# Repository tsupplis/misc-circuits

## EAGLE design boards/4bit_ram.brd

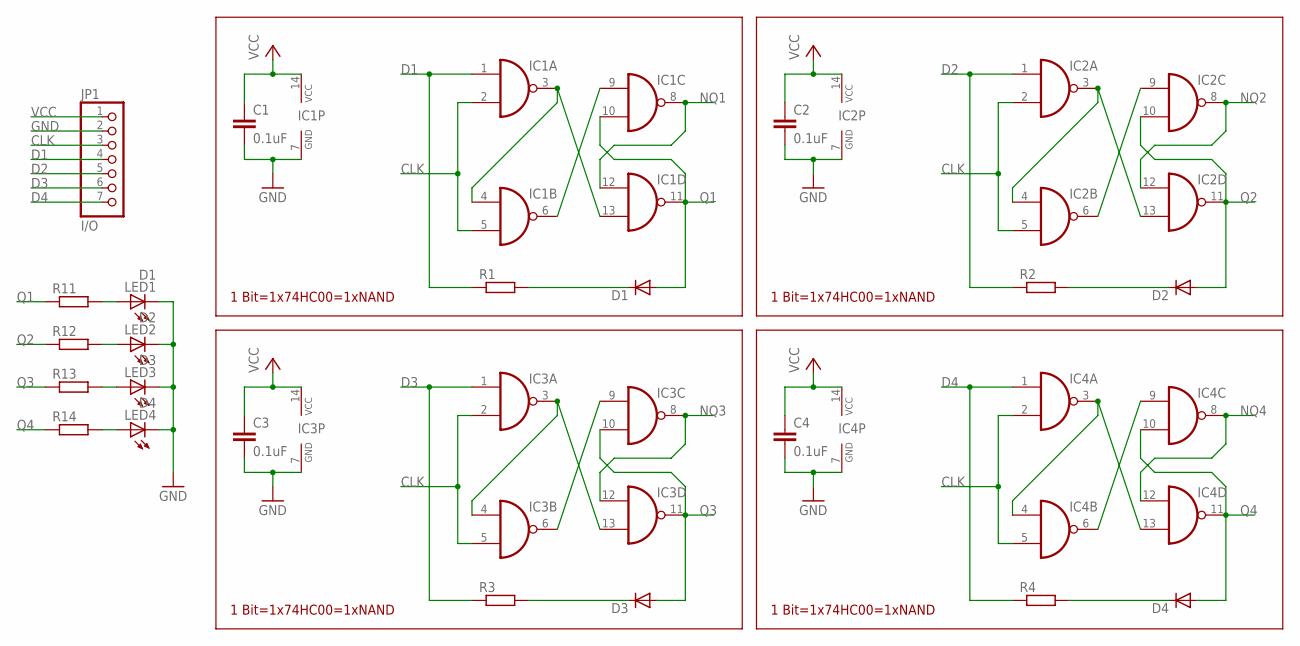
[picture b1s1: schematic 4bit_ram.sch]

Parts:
C1, C2, C3, C4: 0.1uF; C025-025X050
D1, D2, D3, D4: 1N4148DO35-7; DO35-7
IC1, IC2, IC3, IC4: 74HC00N; DIL14
JP1: I/O; 1X07
LED1: D1; LED3MM
LED2: D2; LED3MM
LED3: D3; LED3MM
LED4: D4; LED3MM
R1, R2, R3, R4: 10K; 0204/7
R11, R12, R13, R14: 470; 0204/7

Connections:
CLK: IC1.2 (I1), IC1.5 (I1), IC2.2 (I1), IC2.5 (I1), IC3.2 (I1), IC3.5 (I1), IC4.2 (I1), IC4.5 (I1), JP1.3
D1: IC1.1 (I0), JP1.4, R1.1
D2: IC2.1 (I0), JP1.5, R2.1
D3: IC3.1 (I0), JP1.6, R3.1
D4: IC4.1 (I0), JP1.7, R4.1
GND: C1.2, C2.2, C3.2, C4.2, IC1.7 (GND), IC2.7 (GND), IC3.7 (GND), IC4.7 (GND), JP1.2, LED1.K (C), LED2.K (C), LED3.K (C), LED4.K (C)
unnamed: D1.C, R1.2
unnamed: IC3.6 (O), IC3.9 (I0)
unnamed: IC1.3 (O), IC1.4 (I0), IC1.13 (I1)
unnamed: IC1.6 (O), IC1.9 (I0)
unnamed: IC2.3 (O), IC2.4 (I0), IC2.13 (I1)
unnamed: D2.C, R2.2
unnamed: IC2.6 (O), IC2.9 (I0)
unnamed: IC4.6 (O), IC4.9 (I0)
unnamed: LED1.A, R11.2
unnamed: IC3.3 (O), IC3.4 (I0), IC3.13 (I1)
unnamed: D3.C, R3.2
unnamed: IC4.3 (O), IC4.4 (I0), IC4.13 (I1)
unnamed: D4.C, R4.2
unnamed: LED2.A, R12.2
unnamed: LED3.A, R13.2
unnamed: LED4.A, R14.2
NQ1: IC1.8 (O), IC1.12 (I0)
NQ2: IC2.8 (O), IC2.12 (I0)
NQ3: IC3.8 (O), IC3.12 (I0)
NQ4: IC4.8 (O), IC4.12 (I0)
Q1: D1.A, IC1.10 (I1), IC1.11 (O), R11.1
Q2: D2.A, IC2.10 (I1), IC2.11 (O), R12.1
Q3: D3.A, IC3.10 (I1), IC3.11 (O), R13.1
Q4: D4.A, IC4.10 (I1), IC4.11 (O), R14.1
VCC: C1.1, C2.1, C3.1, C4.1, IC1.14 (VCC), IC2.14 (VCC), IC3.14 (VCC), IC4.14 (VCC), JP1.1

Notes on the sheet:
1 Bit=1x74HC00=1xNAND

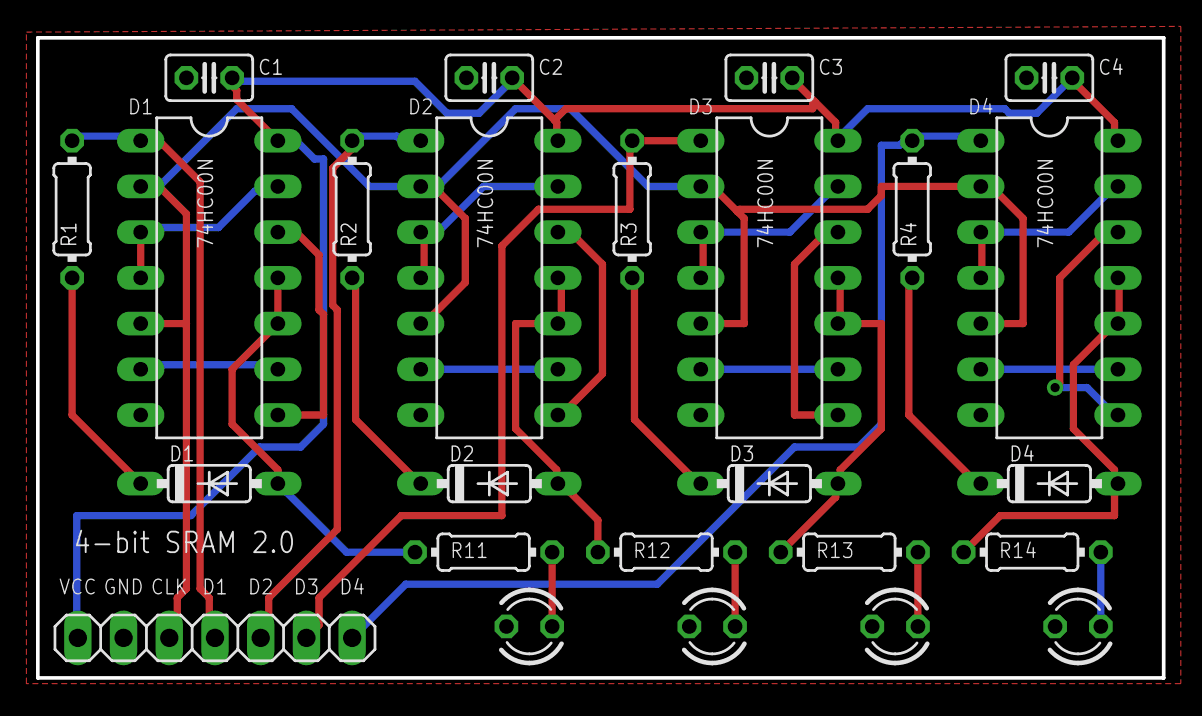
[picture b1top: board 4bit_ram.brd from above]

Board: 2 copper layers, 62.5 x 35.6 mm, 25 parts (0 on the bottom side), 31 nets.

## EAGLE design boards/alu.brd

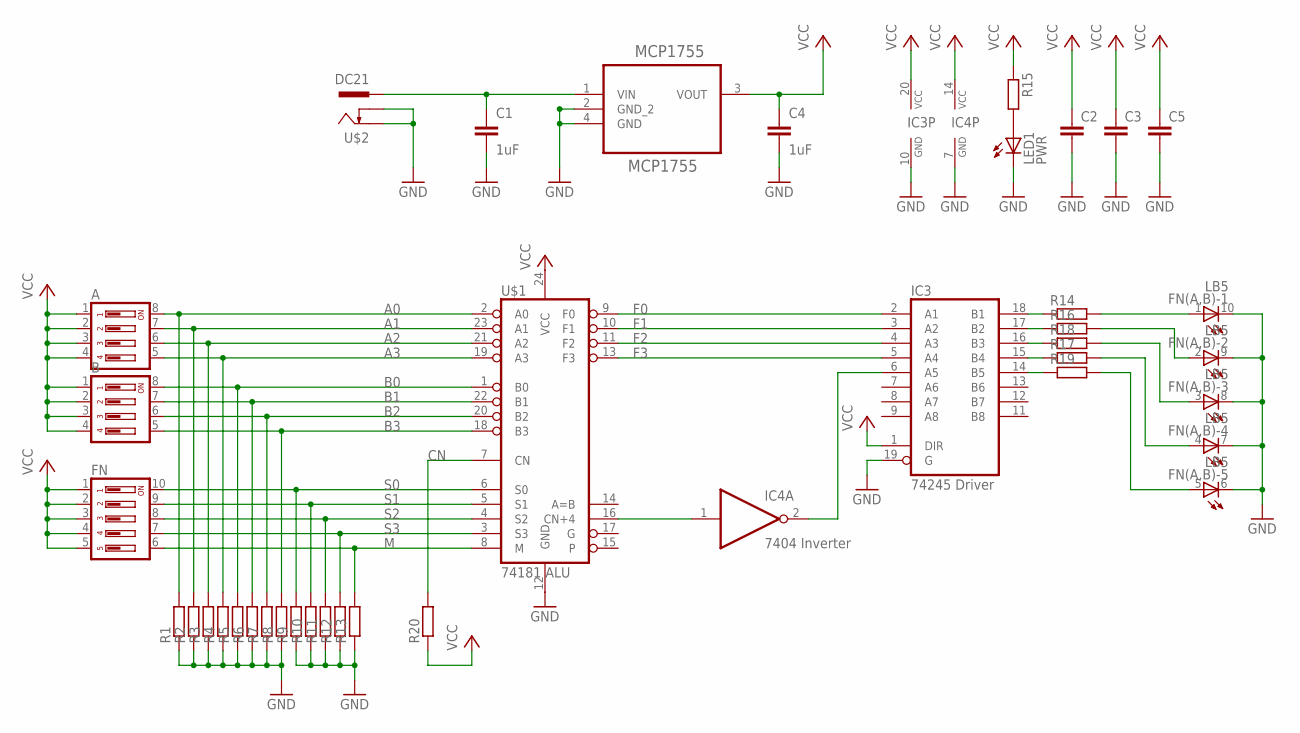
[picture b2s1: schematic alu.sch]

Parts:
A: DS04; DS-04
B: DS04; DS-04
C1, C4: 1uF; C0805
C2, C3, C5: C-EUC0805; C0805
FN: DS05; DS-05
FN(A,B): LB5
IC3: 74245 Driver; DIL20
IC4: 7404 Inverter; DIL14
LED1: PWR; LED3MM
MCP1755: MCP1755; SOT230P700X180-4N
R1, R2, R3, R4, R5, R6, R7, R8, R9, R10, R11, R12, R13, R14, R16, R17, R18, R19, R20: R-EU_R0805; R0805
R15: 470; R0805
U$1: 74181 ALU; DIL24
U$2: DC21; DCSKT

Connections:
!CN+4: IC3.6 (A5), IC4.2 (O)
+VRAW: C1.1, MCP1755.1 (VIN), U$2.1
A0: A.8, R1.2, U$1.2 (A0)
A1: A.7, R2.2, U$1.23 (A1)
A2: A.6, R3.2, U$1.21 (A2)
A3: A.5, R4.2, U$1.19 (A3)
B0: B.8, R5.2, U$1.1 (B0)
B1: B.7, R6.2, U$1.22 (B1)
B2: B.6, R7.2, U$1.20 (B2)
B3: B.5, R8.2, U$1.18 (B3)
CN: R20.2, U$1.7 (CN)
CN+4: IC4.1 (I), U$1.16 (CN+4)
F0: IC3.2 (A1), U$1.9 (F0)
F1: U$1.10 (F1)
F2: IC3.4 (A3), U$1.11 (F2)
F3: IC3.5 (A4), U$1.13 (F3)
GND: C1.2, C2.2, C3.2, C4.2, C5.2, FN(A,B).6 (C), FN(A,B).7 (C), FN(A,B).8 (C), FN(A,B).9 (C), FN(A,B).10 (C), IC3.10 (GND), IC3.19 (G), IC4.7 (GND), LED1.K (C), MCP1755.2 (GND_2), MCP1755.4 (GND), R1.1, R2.1, R3.1, R4.1, R5.1, R6.1, R7.1, R8.1, R9.1, R10.1, R11.1, R12.1, R13.1, U$1.12 (GND), U$2.2, U$2.3
M: FN.6, R13.2, U$1.8 (M)
unnamed: IC3.18 (B1), R14.1
unnamed: LED1.A, R15.2
unnamed: IC3.17 (B2), R16.1
unnamed: IC3.16 (B3), R18.1
unnamed: IC3.15 (B4), R17.1
unnamed: IC3.14 (B5), R19.1
unnamed: FN(A,B).1 (A), R14.2
unnamed: FN(A,B).2 (A), R16.2
unnamed: FN(A,B).3 (A), R18.2
unnamed: FN(A,B).4 (A), R17.2
unnamed: FN(A,B).5 (A), R19.2
S0: FN.10, R9.2, U$1.6 (S0)
S1: FN.9, R10.2, U$1.5 (S1)
S2: FN.8, R11.2, U$1.4 (S2)
S3: FN.7, R12.2, U$1.3 (S3)
VCC: A.1, A.2, A.3, A.4, B.1, B.2, B.3, B.4, C2.1, C3.1, C4.1, C5.1, FN.1, FN.2, FN.3, FN.4, FN.5, IC3.1 (DIR), IC3.20 (VCC), IC4.14 (VCC), MCP1755.3 (VOUT), R15.1, R20.1, U$1.24 (VCC)

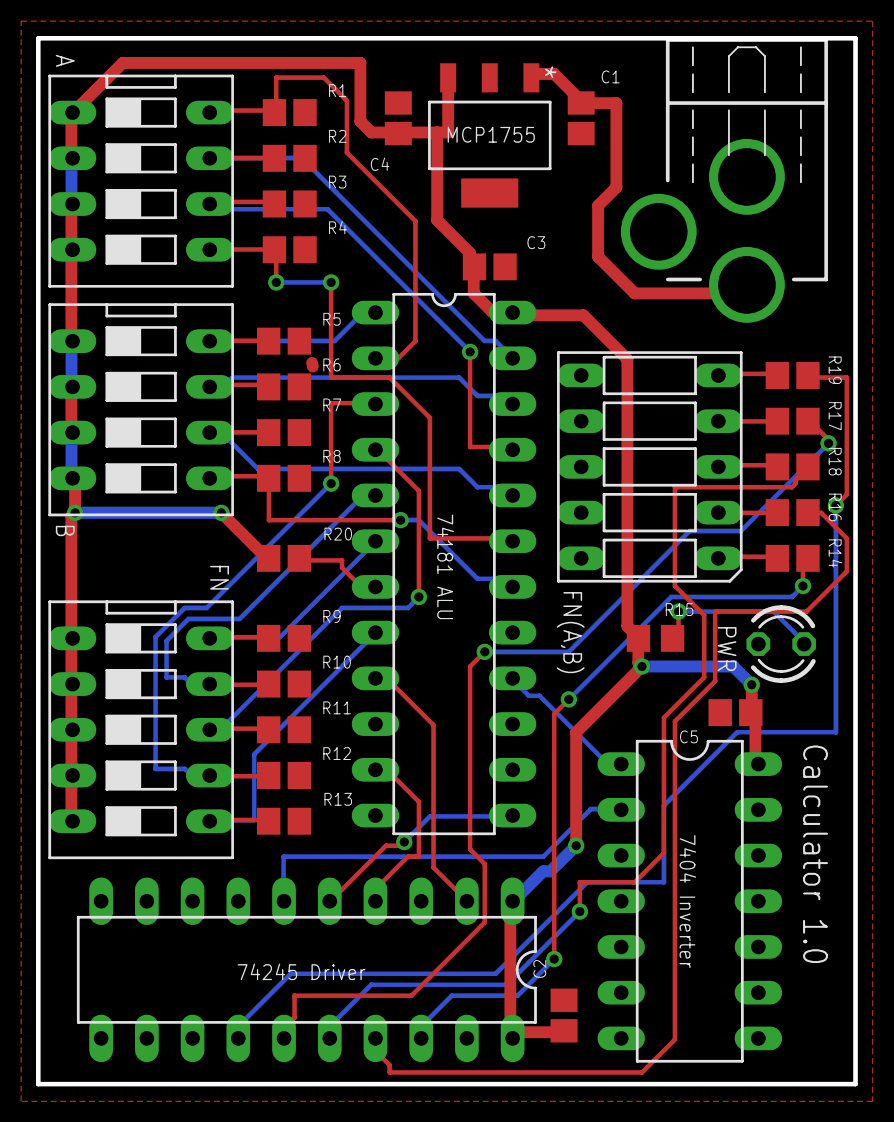
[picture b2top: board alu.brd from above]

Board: 2 copper layers, 45.4 x 58.1 mm, 35 parts (0 on the bottom side), 33 nets.

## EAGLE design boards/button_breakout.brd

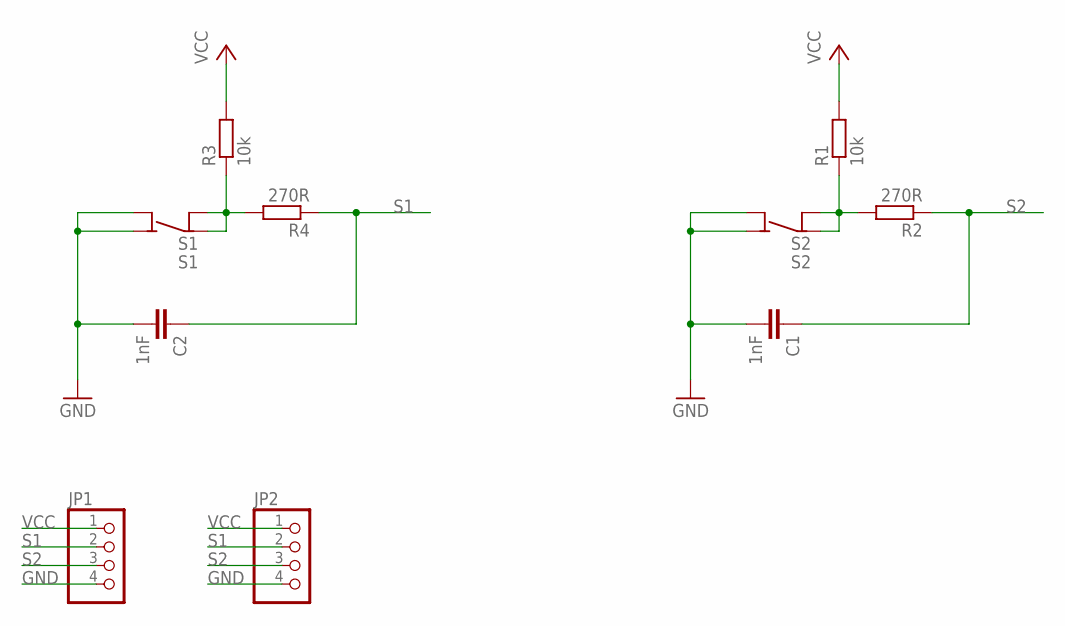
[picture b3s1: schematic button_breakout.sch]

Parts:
C1, C2: 1nF; C0805
JP1, JP2: PINHD-1X4; 1X04
R1, R3: 10k; R0805
R2, R4: 270R; R0805
S1: S1; 6MMTACTILE_4PIN
S2: S2; 6MMTACTILE_4PIN

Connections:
GND: C1.2, C2.2, JP1.4, JP2.4, S1.A1 (NO), S1.A2 (NO), S2.A1 (NO), S2.A2 (NO)
unnamed: R3.1, R4.2, S1.B1 (COM), S1.B2 (COM)
unnamed: R1.1, R2.2, S2.B1 (COM), S2.B2 (COM)
S1: C2.1, JP1.2, JP2.2, R4.1
S2: C1.1, JP1.3, JP2.3, R2.1
VCC: JP1.1, JP2.1, R1.2, R3.2

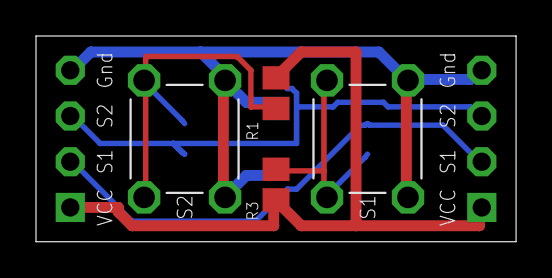
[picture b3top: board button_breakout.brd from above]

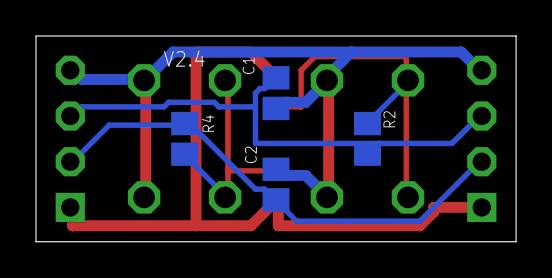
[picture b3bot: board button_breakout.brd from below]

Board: 2 copper layers, 26.7 x 11.4 mm, 10 parts (4 on the bottom side), 6 nets.

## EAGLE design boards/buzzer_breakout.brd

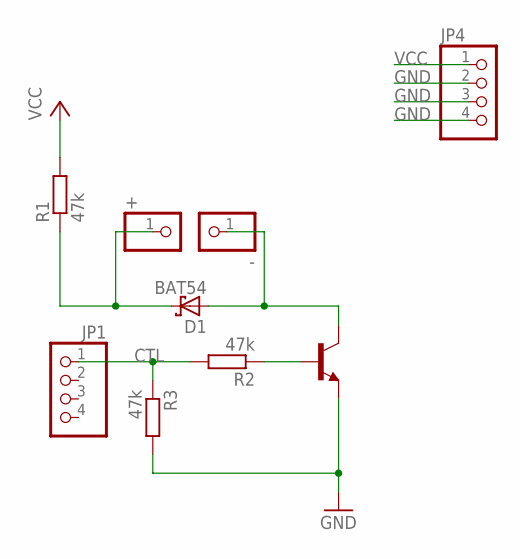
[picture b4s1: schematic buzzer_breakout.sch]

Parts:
+: PINHD-1X1; 1X01
-: PINHD-1X1; 1X01
D1: BAT54; SOT23
JP1, JP4: PINHD-1X4; 1X04
R1, R2, R3: 47k; R0805
T1: BC817-16-NPN-SOT23-BEC; SOT23-BEC

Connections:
CTL: JP1.1, R2.2, R3.1
GND: JP4.2, JP4.3, JP4.4, R3.2, T1.E
unnamed: +.1, D1.3 (C), R1.1
unnamed: -.1, D1.1 (A), T1.C
unnamed: R2.1, T1.B
VCC: JP4.1, R1.2

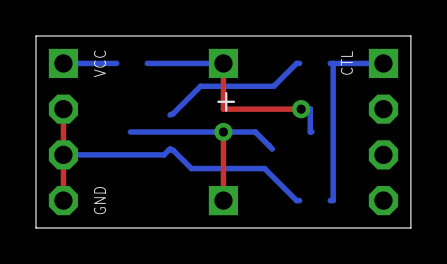
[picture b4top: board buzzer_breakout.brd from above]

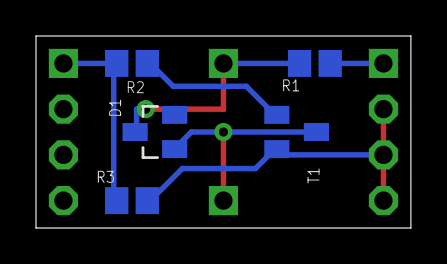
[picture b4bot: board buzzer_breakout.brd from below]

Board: 2 copper layers, 20.8 x 10.7 mm, 9 parts (5 on the bottom side), 6 nets.

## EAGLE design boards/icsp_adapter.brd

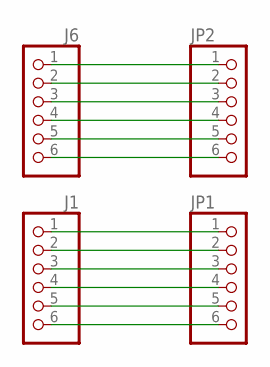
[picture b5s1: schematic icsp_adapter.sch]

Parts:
J1, J6: PH1X650MIL; PH1X6_50MIL
JP1, JP2: PINHD-1X6; 1X06

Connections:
unnamed: J6.1, JP2.1
unnamed: J6.2, JP2.2
unnamed: J6.3, JP2.3
unnamed: J6.4, JP2.4
unnamed: J6.5, JP2.5
unnamed: J6.6, JP2.6
unnamed: J1.1, JP1.1
unnamed: J1.2, JP1.2
unnamed: J1.3, JP1.3
unnamed: J1.4, JP1.4
unnamed: J1.5, JP1.5
unnamed: J1.6, JP1.6

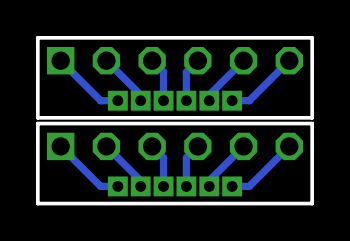
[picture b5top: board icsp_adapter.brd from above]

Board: 2 copper layers, 15.2 x 9.2 mm, 4 parts (0 on the bottom side), 12 nets.

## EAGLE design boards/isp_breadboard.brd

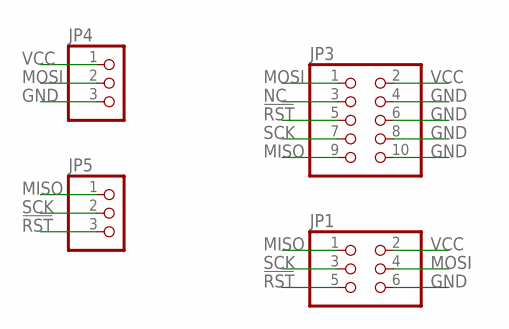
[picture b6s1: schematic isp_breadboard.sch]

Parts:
JP1: PINHD-2X3; 2X03
JP3: PINHD-2X5; 2X05
JP4, JP5: PINHD-1X3; 1X03

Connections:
!RST: JP1.5, JP3.5, JP5.3
GND: JP1.6, JP3.4, JP3.6, JP3.8, JP3.10, JP4.3
MISO: JP1.1, JP3.9, JP5.1
MOSI: JP1.4, JP3.1, JP4.2
NC: JP3.3
SCK: JP1.3, JP3.7, JP5.2
VCC: JP1.2, JP3.2, JP4.1

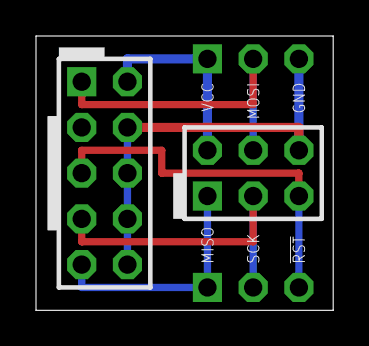
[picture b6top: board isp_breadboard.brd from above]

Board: 2 copper layers, 16.5 x 15.2 mm, 4 parts (0 on the bottom side), 6 nets.

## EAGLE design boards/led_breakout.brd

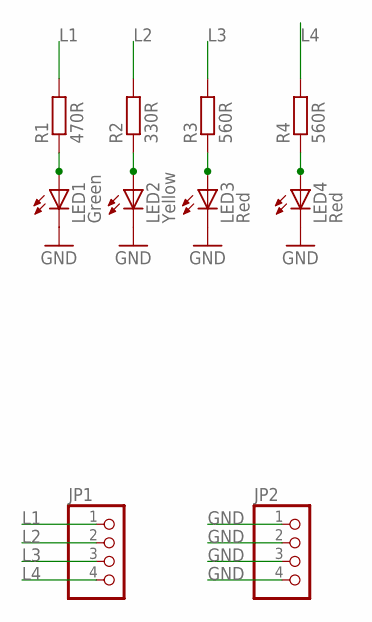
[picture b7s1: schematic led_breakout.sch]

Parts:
JP1, JP2: PINHD-1X4; 1X04
LED1: Green; CHIPLED_1206
LED2: Yellow; CHIPLED_1206
LED3, LED4: Red; CHIPLED_1206
R1: 470R; R0805
R2: 330R; R0805
R3, R4: 560R; R0805

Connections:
GND: JP2.1, JP2.2, JP2.3, JP2.4, LED1.C, LED2.C, LED3.C, LED4.C
L1: JP1.1, R1.2
L2: JP1.2, R2.2
L3: JP1.3, R3.2
L4: JP1.4, R4.2
unnamed: LED3.A, R3.1
unnamed: LED4.A, R4.1
unnamed: LED1.A, R1.1
unnamed: LED2.A, R2.1

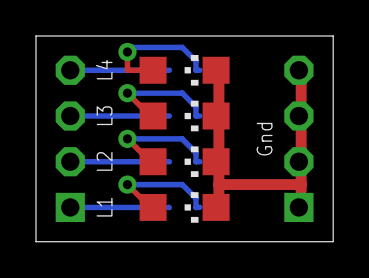
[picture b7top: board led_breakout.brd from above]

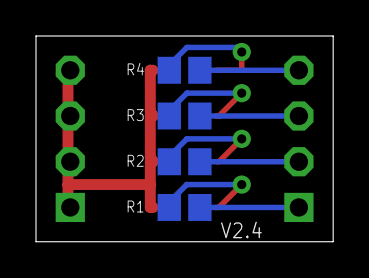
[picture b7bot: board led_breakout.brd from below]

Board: 2 copper layers, 16.5 x 11.4 mm, 10 parts (4 on the bottom side), 9 nets.
